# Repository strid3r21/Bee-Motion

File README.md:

# Bee Motion

## **Visit our** [Discord](https://tinyurl.com/Bee-Motion-Discord-Git)
## **Buy on** [Tindie](https://www.tindie.com/products/smartbee/bee-motion-esp32-pir-motion-sensor/)
________________________________________________________________________________________________________________________

# Video Overview

________________________________________________________________________________________________________________________

# Pinouts

________________________________________________________________________________________________________________________

# Programming on Arduino

## Add the Espressif ESP32 arduino board library to Arduino IDE
File > Preferences > at the bottom "Additional Board Manager URLS" paste in this url
https://raw.githubusercontent.com/espressif/arduino-esp32/gh-pages/package_esp32_index.json 
 
From there you will be able to search and add the ESP32 board library from the board library search bar. install the ESP32 library by Espressif and make sure you're using version number 2.0.5 or later. You will then be able to select your Bee Motion from the board manager.

## How to program the Bee Motion
In order to program the Bee Motion you need to put it into download mode. To do so all you need to do is connect the USB-C cable and then press and hold the boot button. with the boot button being held down, press the reset button and release. then you can release the boot button. this will put the Bee Motion into download mode which will allow it to be programmed. Then for the board, select "Bee Motion" from the board manager.

# Battery Life Information
_______________________________________________________________________________________________________________________

**On battery power the Bee Motion uses about 80mAH while on WiFi**

**During deepsleep it uses about 45uA!**

**For sake of an example, if paired with a 1500mAh LiPo battery and triggered 20x a day with Wifi it would last for over a year!**

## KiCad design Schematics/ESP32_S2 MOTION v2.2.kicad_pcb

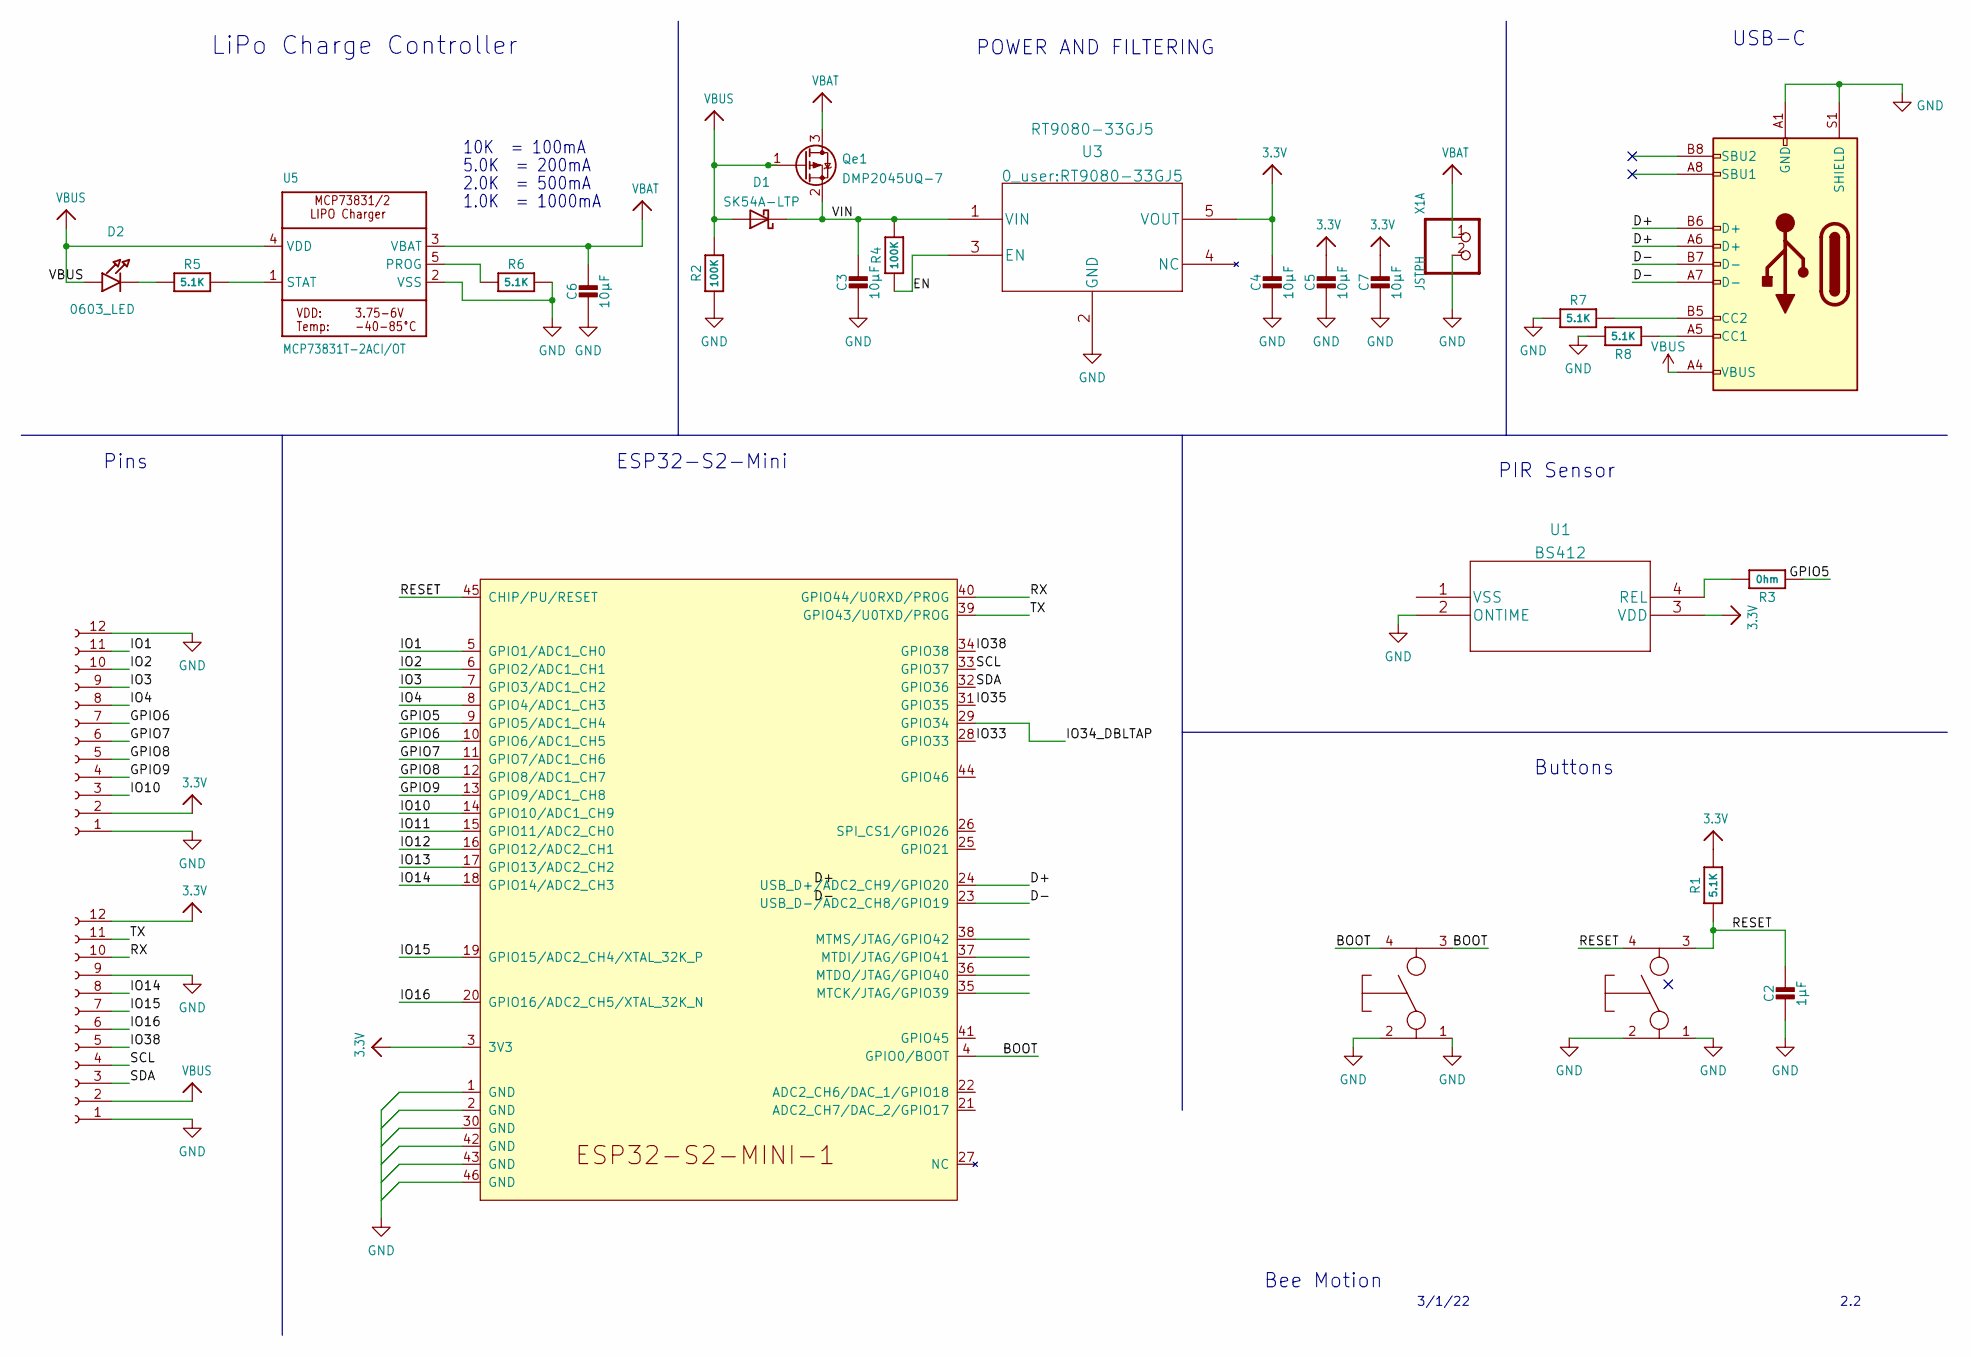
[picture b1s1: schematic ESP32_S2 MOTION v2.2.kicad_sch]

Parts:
C2: 1µF; C_0603_1608Metric
C3, C4, C5, C6, C7: 10µF; C_0603_1608Metric
D1: SK54A-LTP; D_SOD-323
D2: 0603_LED; LED_0603_1608Metric
J1, J3: Conn_01x04_Female; PinHeader_1x12_P2.54mm_Vertical
J2: USB_C_Receptacle_USB2.0; USB_C_Receptacle_Palconn_UTC16-G
Qe1: DMP2045UQ-7; SOT-23
R1, R5, R6, R7, R8: 5.1K; R_0603_1608Metric
R2, R4: 100K; R_0603_1608Metric
R3: 0hm; R_0603_1608Metric
SW1, SW2: TSA343g00-250DZ; TSA343G0 BTN
U1: BS412; 4666
U2: ESP32-S2-MINI-1
U3: RT9080-33GJ5
U5: MCP73831T-2ACI/OT; mcp7831t
X1: JSTPH; JST_PH_S2B-PH-SM4-TB_1x02-1MP_P2.00mm_Horizontal

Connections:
3.3V: C4.1, C5.1, C7.1, J1.2, J3.12, R1.2, U1.3 (VDD), U2.3 (3V3), U3.5 (VOUT)
/BOOT: SW2.3 (K), SW2.4 (A), U2.4 (GPIO0/BOOT)
/D+: J2.A6 (D+), J2.B6 (D+), U2.24 (USB_D+/ADC2_CH9/GPIO20)
/D-: J2.A7 (D-), J2.B7 (D-), U2.23 (USB_D-/ADC2_CH8/GPIO19)
/EN: R4.1, U3.3 (EN)
/GPIO5: R3.1, U2.9 (GPIO5/ADC1_CH4)
/GPIO6: J1.7, U2.10 (GPIO6/ADC1_CH5)
/GPIO7: J1.6, U2.11 (GPIO7/ADC1_CH6)
/GPIO8: J1.5, U2.12 (GPIO8/ADC1_CH7)
/GPIO9: J1.4, U2.13 (GPIO9/ADC1_CH8)
/IO1: J1.11, U2.5 (GPIO1/ADC1_CH0)
/IO2: J1.10, U2.6 (GPIO2/ADC1_CH1)
/IO3: J1.9, U2.7 (GPIO3/ADC1_CH2)
/IO4: J1.8, U2.8 (GPIO4/ADC1_CH3)
/IO10: J1.3, U2.14 (GPIO10/ADC1_CH9)
/IO11: U2.15 (GPIO11/ADC2_CH0)
/IO12: U2.16 (GPIO12/ADC2_CH1)
/IO13: U2.17 (GPIO13/ADC2_CH2)
/IO14: J3.8, U2.18 (GPIO14/ADC2_CH3)
/IO15: J3.7, U2.19 (GPIO15/ADC2_CH4/XTAL_32K_P)
/IO16: J3.6, U2.20 (GPIO16/ADC2_CH5/XTAL_32K_N)
/IO33: U2.28 (GPIO33)
/IO34_DBLTAP: U2.29 (GPIO34)
/IO35: U2.31 (GPIO35)
/IO38: J3.5, U2.34 (GPIO38)
/RESET: C2.1, R1.1, SW1.3 (K), SW1.4 (A), U2.45 (CHIP/PU/RESET)
/RX: J3.10, U2.40 (GPIO44/U0RXD/PROG)
/SCL: J3.4, U2.33 (GPIO37)
/SDA: J3.3, U2.32 (GPIO36)
/TX: J3.11, U2.39 (GPIO43/U0TXD/PROG)
/VIN: C3.1, D1.1 (K), Qe1.2 (S), R4.2, U3.1 (VIN)
unnamed: D2.2, R5.1
unnamed: J2.A5 (CC1), R8.1
unnamed: J2.B5 (CC2), R7.1
unnamed: R3.2, U1.4 (REL)
unnamed: R5.2, U5.1 (STAT)
unnamed: R6.1, U5.5 (PROG)
VBAT: C6.1, Qe1.3 (D), U5.3 (VBAT), X1.1
VBUS: D1.2 (A), D2.1, J2.A4 (VBUS), J2.A9 (VBUS), J2.B4 (VBUS), J2.B9 (VBUS), J3.2, Qe1.1 (G), R2.2, U5.4 (VDD)

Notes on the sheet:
5.0K = 200mA
10K = 100mA
ESP32-S2-Mini
Bee Motion
2.0K = 500mA
Buttons
3/1/22
USB-C
PIR Sensor
Pins
POWER AND FILTERING
1.0K = 1000mA
2.2
LiPo Charge Controller

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
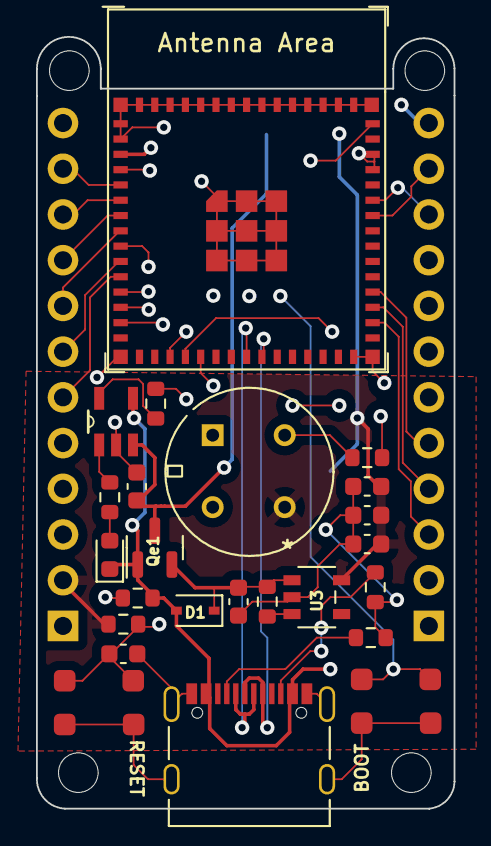
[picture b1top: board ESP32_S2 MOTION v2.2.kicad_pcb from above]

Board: 4 copper layers, 23.2 x 42.9 mm, 27 parts (1 on the bottom side), 34 nets.

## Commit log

2022-05-01 Added Battery Consumption Graphs
2022-05-02 added 3D printed case files
    this is a basic 3D printed case for the Bee Motion. ive included the STL for easy printing on your 3D printer and the Fusion 360 file incase you want to easily modify it for your own needs.
2022-05-02 added links
2022-05-06 Added a Deep Sleep arduino sketch example
2022-05-13 Added video overview
2022-05-13 added how to program info
2022-05-14 fixed discord link
2022-05-18 added some troubleshooting infomaiton
2022-05-18 added photo
2022-05-18 added Photos
2022-05-19 Fixed a typo
2022-06-03 Added additional troubleshooting note.
2022-06-06 Minor tweak
2022-06-06 Adjusted some text.
2022-07-23 added a basic sketch
    this basic sketch will let you monitor motion detection from the serial monitor
2022-07-23 Added basic sketch to monitor PIR Sensor
    this basic sketch lets you monitor the PIR motion detection with the Serial monitor
2022-07-23 added a note to deep sleep sketch
2022-08-19 added micro-python and circuit python support
2022-08-19 moved arduino code into the code folder
2022-08-19 cleaned up README
2022-08-19 readme
2024-02-15 Update Bee Motion Basic.ino
    no idea why i had a wifi begin in there

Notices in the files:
parts and their libraries:
Copyright 2021 Accelerated Designs. All rights reserved.
